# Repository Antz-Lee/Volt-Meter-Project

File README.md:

# Volt-Meter-Project
Creating a voltmeter that displays the input voltage on an LCD display by using an ATmega328pb chip

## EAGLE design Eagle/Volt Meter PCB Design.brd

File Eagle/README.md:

# Schematic and Board Layout
The schematic layout created on the EAGLE program. In regards, to the PCB Layout. the 16x2 LCD desplay isnt 
mounted directly onto the board, however, it will use connect cables so it could be applicable to be mounted on a frame.

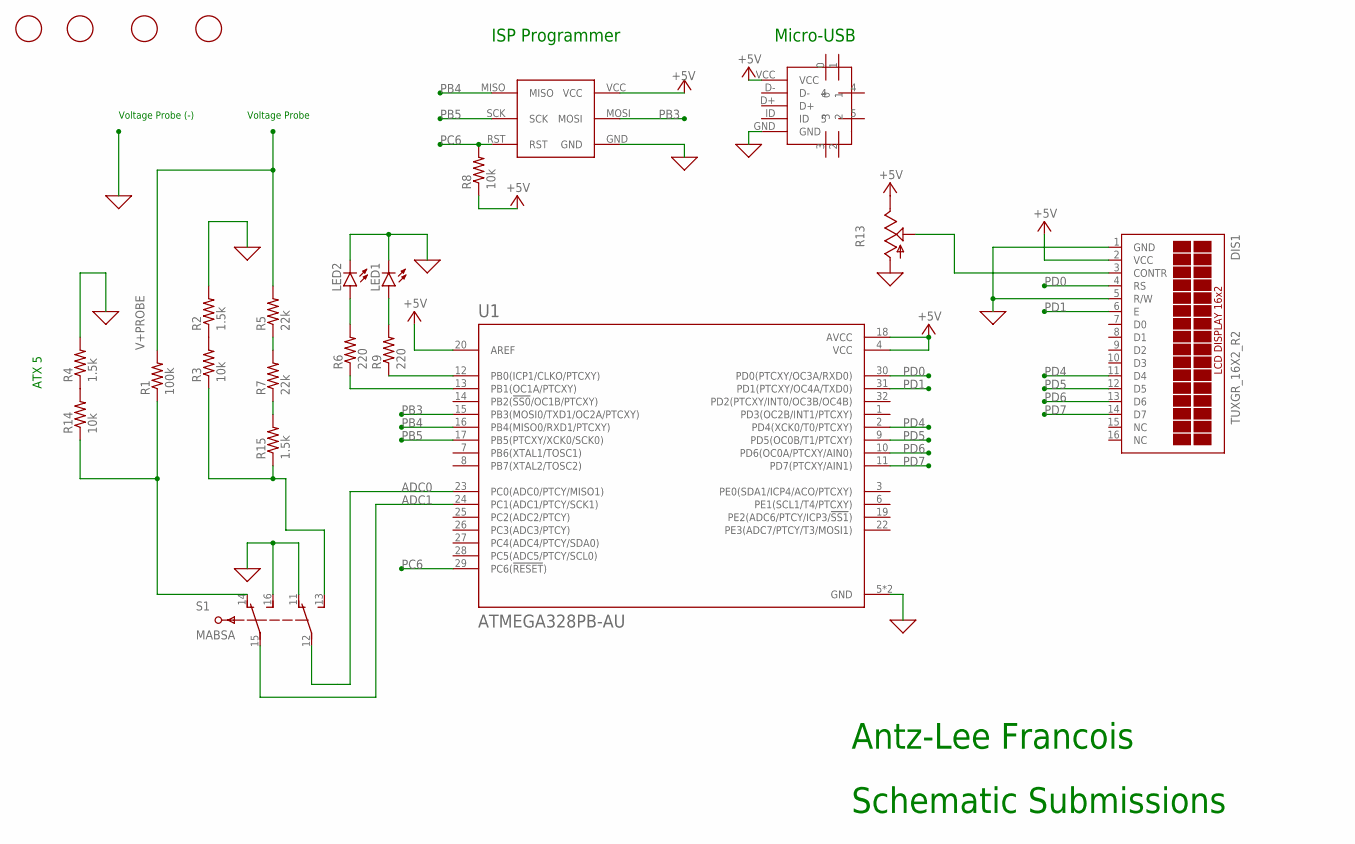
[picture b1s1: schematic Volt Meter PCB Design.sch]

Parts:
AVR-ISP: AVR-ISP
DIS1: TUXGR_16X2_R2
LED1, LED2: LED5MM
MICROUSB1: MICROUSB1
R1: 100k; M0805
R2, R4, R15: 1.5k; M0805
R3, R8, R14: 10k; M0805
R5, R7: 22k; M0805
R6, R9: 220; M0805
R13: TRIM_US-B25P; B25P
S1: MABSA
U1: ATMEGA328PB-AU; QFP80P900X900X120-32N
U$1, U$2, U$3, U$4: FIDUCIAL; FIDUCIAL_1MM

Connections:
0: AVR-ISP.GND, DIS1.1 (GND), DIS1.5 (R/W), LED1.K (C), LED2.K (C), MICROUSB1.GND, R2.2, R4.2, R13.A, S1.11, S1.16, U1.5 (GND), U1.21 (GND)
+5V: AVR-ISP.VCC, DIS1.2 (VCC), MICROUSB1.VCC, R8.1, R13.E, U1.4 (VCC), U1.18 (AVCC), U1.20 (AREF)
ADC0: S1.12, U1.23 (PC0(ADC0/PTCY/MISO1))
ADC1: S1.15, U1.24 (PC1(ADC1/PTCY/SCK1))
ATX5: R1.1, R14.1, S1.14
ATX10: R5.1, R7.2
HLED: LED1.A, R9.2
HLED_PWR: R9.1, U1.12 (PB0(ICP1/CLKO/PTCXY))
LCD_DIMMER: DIS1.3 (CONTR), R13.S
LLED: LED2.A, R6.2
LLED_PWR: R6.1, U1.13 (PB1(OC1A/PTCXY))
unnamed: R4.1, R14.2
unnamed: R2.1, R3.2
unnamed: R7.1, R15.2
unnamed: R3.1, R15.1, S1.13
PB3: AVR-ISP.MOSI, U1.15 (PB3(MOSI0/TXD1/OC2A/PTCXY))
PB4: AVR-ISP.MISO, U1.16 (PB4(MISO0/RXD1/PTCXY))
PB5: AVR-ISP.SCK, U1.17 (PB5(PTCXY/XCK0/SCK0))
PC6: AVR-ISP.RST, R8.2, U1.29 (PC6(!RESET!))
PD0: DIS1.4 (RS), U1.30 (PD0(PTCXY/OC3A/RXD0))
PD1: DIS1.6 (E), U1.31 (PD1(PTCXY/OC4A/TXD0))
PD4: DIS1.11 (D4), U1.2 (PD4(XCK0/T0/PTCXY))
PD5: DIS1.12 (D5), U1.9 (PD5(OC0B/T1/PTCXY))
PD6: DIS1.13 (D6), U1.10 (PD6(OC0A/PTCXY/AIN0))
PD7: DIS1.14 (D7), U1.11 (PD7(PTCXY/AIN1))
V+PROBE: R1.2, R5.2

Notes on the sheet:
Antz-Lee Francois
Schematic Submissions
Voltage Probe
Voltage Probe (-)
ISP Programmer
Micro-USB
ATX 5

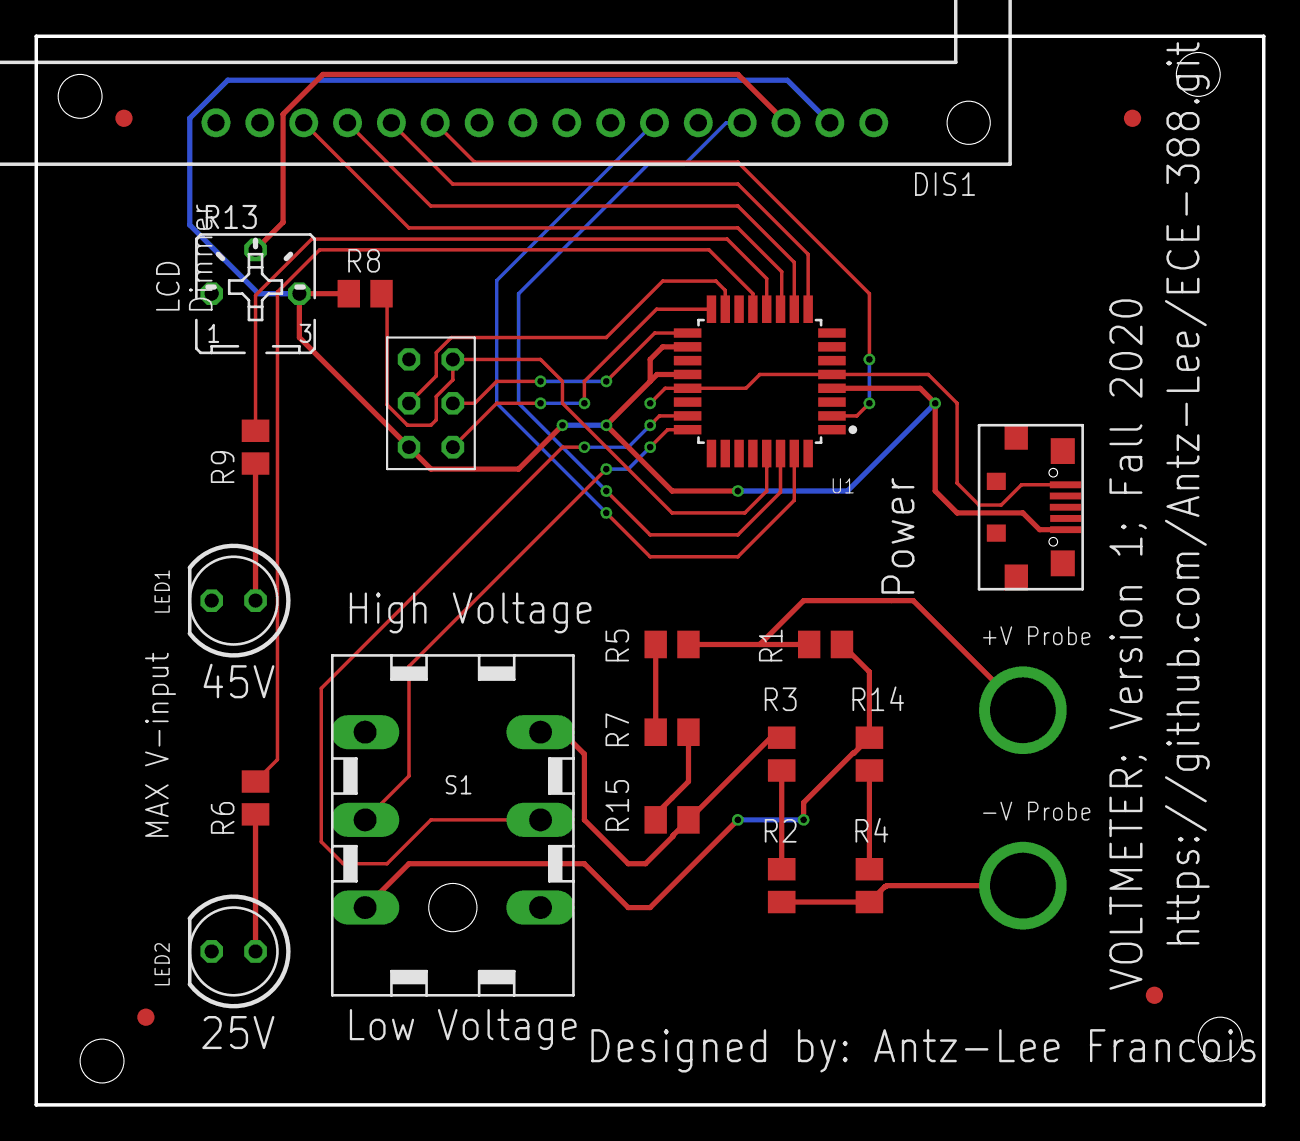
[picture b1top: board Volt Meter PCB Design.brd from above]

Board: 2 copper layers, 71.1 x 61.9 mm, 23 parts (0 on the bottom side), 26 nets.

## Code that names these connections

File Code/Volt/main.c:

#include <stdlib.h>
#include <avr/io.h>
#include <stdint.h>
#include <avr/delay.h>
#include <string.h>
#define _BV(n) (1 << n)
#define F_CPU 4000000
#define LED5x PB1
#define LED10x PB0
#define LCD_Port PORTD		//Define LCD Port (PORTA, PORTB, PORTC, PORTD)
#define LCD_DPin  DDRD		//Define 4-Bit Pins (PD4-PD7 at PORT D)
#define RSPIN PD0			//RS Pin
#define ENPIN PD1 			//E Pin

uint16_t adc_read(uint16_t adcx);         // Allows the ADC ports to be read
void adc_init();                          // Enables the ADC port
void LCD_Init (void);                     // Enables the LCD    
void LCD_Clear();                         // CLears LCD screen and puts LCD cursor at line 1
void LCD_Print (char *str);               // Prints string on LCD
void LCD_LineJmp( unsigned char cmnd );   // Allows LCD Cursor to position at line 1/2
void LED (char *command );                // LED commands


int main(void)
{
	adc_init();        // Enables the ADC port
	LED("Enable");     // Enables the LED 
	LCD_Init();        // Enables the LCD 
	
    // Setting variables
	volatile uint16_t Vread10x = 0;
	volatile uint16_t Vread5x = 0;

	volatile uint16_t ADC0;
	volatile uint16_t ADC1;
    
	// Setting I.D variables
	volatile double Vres = 5.0/1024;
	volatile double Error = .88;    //0.9253382438;
	
	// Voltage difference 
	volatile double Vmeas10x, Vmeas5x;
		
	while(1)
	{
			// Setting the ADC read out pin 
			Vread10x = adc_read(0); 
			Vread5x = adc_read(1);   
					    
			// Measuring the Voltage sum
			Vmeas5x =  (float)Vread5x * Vres * 5 /Error;            //Vdiff for Att 5x
			Vmeas10x = (float)Vread10x * Vres * 10 / Error;        //Vdiff for Att 10x
			
			//value to be displayed
			char DispVmeas5x[6];
			char DispVmeas10x[6];
			snprintf(DispVmeas5x,6,"%f", Vmeas5x);
			snprintf(DispVmeas10x,6,"%f", Vmeas10x);
			
			ADC0= Vread10x;
			ADC1= Vread5x;
			    
			//Switch 
			 if (ADC0 == 0 && ADC1 == 0)   // when connected theres no input
			  {
				  LCD_Clear();                              //clears and starts at position 1
				  LCD_Print("         Connected to GND");
				  LCD_LineJmp(0xC0);                        //Jumps to line two
				  LCD_Print("Unit (V): ");
				  LCD_Print(DispVmeas5x);                   //Displays Value
				  LED("AOF");                               // Turns off all LED
				  _delay_ms(1500);
				  LED("AON");                               // Turns on all LED
				  _delay_ms(15000);
			  }
  			 else if(ADC0 == ADC1 && ADC0 > 0 )  //WARNING CHECK Input
			  {  
				  for(int i=0; i < 3; i++)
				  {  //Flashes
				   LED("AON");                             //Turns on all LED
				   LCD_Clear();                            // clears and starts at position 1
				   LCD_Print("           !!WARNING!!");
				   LCD_LineJmp(0xC0);                      //Jumps to Line 2
				   LCD_Print("   CHECK INPUT");
				   _delay_ms(5000);
				   LCD_Clear();                            // clears and starts at position 1
				   LED("AOF");                             //Turns off all LED
			       _delay_ms(5000);
				  }
			   } 
			  else if(ADC0 > 0 && ADC1 < ADC0)   //10x Position
			  {
				  LED("Atx10");                              //Turns on 10x LED
				  LCD_Clear();                               // clears and starts at position 1
				  LCD_Print("         HighVoltage <45V");
				  LCD_LineJmp(0xC0);                         //jumps to line 2
				  LCD_Print("Unit (V): ");
				  LCD_Print(DispVmeas10x);                   //Displays Value
				  _delay_ms(15000);
			  }
			  else  //if(ADC1 > 0 && ADC1 > ADC0)       
			  {    //5x Position
				   LED("Atx5");                              // Turn on 5x LED
				   LCD_Clear();                              // clears and starts at position 1
				   LCD_Print("         Low Voltage <25V");
				   LCD_LineJmp(0xC0);                        //jumps to line two
				   LCD_Print("Unit (V): ");
				   LCD_Print(DispVmeas5x);                   // Displays Value
				   _delay_ms(15000);   
			  } 
		}
}

void LED (char *command )
{
	if (command == "Enable")
	{
		DDRB |= _BV(LED10x);
		DDRB |= _BV(LED5x);
	}
	else if(command == "Atx10")
	{
		 PORTB &= ~(1<<LED5x);       // Turns off Low Voltage Light
		 PORTB |= _BV(LED10x);      //turns on High Voltage LED
	}
	else if (command == "Atx5")
	{
		 PORTB &= ~(1<<LED10x);    //turns off High Voltage LED
		 PORTB |= _BV(LED5x);     // Turns on Low Voltage Light
	}
	else if(command == "AOF")
	{
		PORTB &= ~(1<<LED10x);    //turns off High Voltage LED
		PORTB &= ~(1<<LED5x);    // Turns off Low Voltage Light
	}
	else if(command == "AON")
	{
		PORTB |= _BV(LED10x);     //turns on High Voltage LED
		PORTB |= _BV(LED5x);     //turns on Low Voltage LED
	}
	else if(command == "Blink")
	{
		PORTB &= ~(1<<LED10x);    //turns off High Voltage LED
		PORTB &= ~(1<<LED5x);    // Turns off Low Voltage Light
		_delay_ms(1500);
		PORTB |= _BV(LED10x);     //turns on High Voltage LED
		PORTB |= _BV(LED5x);     //turns on Low Voltage LED
	}
	else
	{
		return 0;
	}
}

void LCD_Init (void)
{
	LCD_DPin = 0xFF;		//Control LCD Pins (D4-D7)
	_delay_ms(15);		//Wait before LCD activation
	LCD_LineJmp(0x02);	//4-Bit Control
	LCD_LineJmp(0x28);       //Control Matrix @ 4-Bit
	LCD_LineJmp(0x0c);       //Disable Cursor
	LCD_LineJmp(0x06);       //Move Cursor
	LCD_LineJmp(0x01);       //Clean LCD
	_delay_ms(2);
}

void LCD_LineJmp( unsigned char cmnd )
{
	LCD_Port = (LCD_Port & 0x0F) | (cmnd & 0xF0);
	LCD_Port &= ~ (1<<RSPIN);
	LCD_Port |= (1<<ENPIN);
	_delay_us(1);
	LCD_Port &= ~ (1<<ENPIN);
	_delay_us(200);
	LCD_Port = (LCD_Port & 0x0F) | (cmnd << 4);
	LCD_Port |= (1<<ENPIN);
	_delay_us(1);
	LCD_Port &= ~ (1<<ENPIN);
	_delay_ms(2);
}

void LCD_Clear()
{
	LCD_LineJmp (0x01);		//Clear LCD
	_delay_ms(2);			//Wait to clean LCD
	LCD_LineJmp (0x80);		//Move to Position Line 1, Position 1
}


void LCD_Print (char *str)
{
	int i;
	for(i=0; str[i]!=0; i++  )
	{
		LCD_Port = (LCD_Port & 0x0F) | (str[i] & 0xF0);
		LCD_Port |= (1<<RSPIN);
		LCD_Port|= (1<<ENPIN);
		_delay_us(1);
		LCD_Port &= ~ (1<<ENPIN);
		_delay_us(200);
		LCD_Port = (LCD_Port & 0x0F) | (str[i] << 4);
		LCD_Port |= (1<<ENPIN);
		_delay_us(1);
		LCD_Port &= ~ (1<<ENPIN);
		_delay_ms(2);
	}
}

// Enables 
void adc_init()
{
	ADMUX = (1<<REFS0) | (0<<REFS1);
	// ADC Enable and prescaler of 128
	// 8000000/128 = 62500
	ADCSRA = (1<<ADEN)|(1<<ADPS2)|(1<<ADPS1)|(1<<ADPS0);
}

// reads the ADC port
uint16_t adc_read(uint16_t adcx)
{
	ADMUX &= 0xf0;
	ADMUX |= adcx;
	
	ADCSRA |= _BV(ADSC);
	while( ADCSRA & _BV(ADSC)  );
	
	return (double)ADC;
}

/*//Write on a specific location
void LCD_Printpos (char row, char pos, char *str)
{
	if (row == 0 && pos<16)
	LCD_LineJmp((pos & 0x0F)|0x80);
	else if (row == 1 && pos<16)
	LCD_LineJmp((pos & 0x0F)|0xC0);
	LCD_Print(str);
}    */

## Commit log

2020-11-26 Create Eagle Schematic
    This folder holds the schematic design as well as the PCB board layout processed on Eagle
2020-11-26 Create Eagle Schematic
2020-11-26 Schematic
2020-11-28 test
2020-11-28 test 2
2020-11-28 test 3, adding eagle files
2020-11-28 test 4, uploaded screen shots
2020-11-28 test 5, fixed cover picture
2020-11-28 test 6, cover pic test
2020-11-28 test 7, eagle design upload
2020-11-28 test 8, read me with pic
2020-11-28 test 11, Test folder.+ATX files
2020-11-28 test 12, add SCH Capture
2020-11-28 tst 12, add eagle read me w/ captures
2020-11-28 tst 13, +captures
2020-11-28 tst 14, +readme files folders
2020-11-29 test 15, Update
2020-11-30 tst 16, +Gerber submission folder
